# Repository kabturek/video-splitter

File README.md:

# Video Splitter

**This design is UNTESTED - the pcb was sent to the fab house 16.10.2016.**

This is a simple 2 channel video splitter for FPV use (but can be use with any analog signal).
It uses servo connectors for video in/out but you can solder wires directly to
the pads. Power pin is just a passthru between the 3 connectors (and it powers
the regulator). 

## Design

This is really a mashup of 2 reference designs - IA171 and LP2985 so no big
innovation here. According to the datasheet the IA171 can drive to 75ohm loads.

## Power supply

The splitter was designed to be powered by 5-16v if a 3.3v voltage regulator is used (LP2985 or mic5205). 
The IA171 can be powered by 2.8-5.5V so its possible to use it without any voltage regulator if you have a stable 
power supply in that range - bridge pins 1 and 5 (top pins) of the VREG and
applu 2.8-5.5v to any of the 3 pin connectors (middle pin).

## [BOM](BOM.csv)

| "Qty" | "Value"         | "Device"                        | "Package"   | "Parts"             | "Description"         | "Link" |
|-------|-----------------|---------------------------------|-------------|---------------------|-----------------------|----|
| "3"   | ""              | "M03LOCK"                       | "1X03_LOCK" | "VIN, VOUT1, VOUT2" | "Header 3"            | "" |
| "1"   | "0.1uF"         | "CAP0805"                       | "0805"      | "C1"                | "Capacitor"           | "" |
| "1"   | "100uF"         | "CAP_POL3528"                   | "EIA3528"   | "C3"                | "Capacitor Polarized" | "" |
| "1"   | "10nF"          | "CERAMIC-10NF-50V-5%-X7R(0805)" | "C0805"     | "C7"                | "302010175"           | "" |
| "3"   | "22uF"          | "CAP_POL1206"                   | "EIA3216"   | "C2, C4, C6"        | "Capacitor Polarized" | "" |
| "3"   | "75R"           | "RESISTOR0805-RES"              | "0805"      | "R1, R2, R3"        | "Resistor"            | "" |
| "1"   | "IA171"         | "IA171"                         | "SOT23-6"   | "U$1"               | ""                    | "" |
| "1"   | "LP2985-33DBVR" | "PMIC-LP2985-33DBVR(SOT23-5)"   | "SOT-23-5"  | "VREG"              | "310030033"           | "" |

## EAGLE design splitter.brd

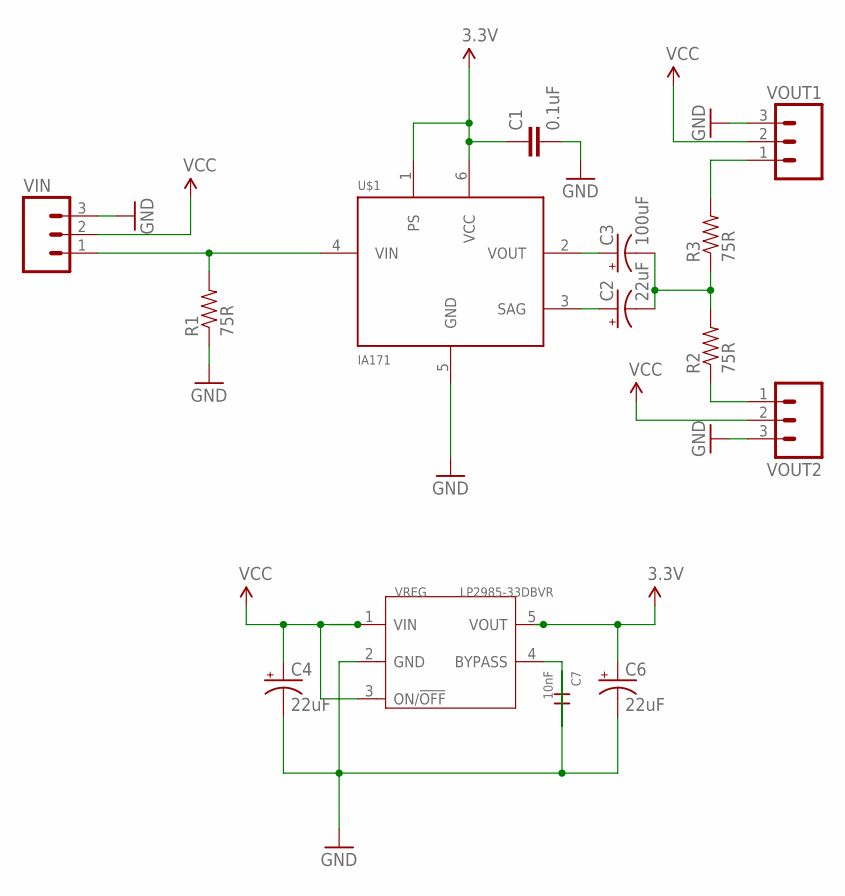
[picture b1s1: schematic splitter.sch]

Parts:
C1: 0.1uF; 0805
C2, C4, C6: 22uF; EIA3216
C3: 100uF; EIA3528
C7: 10nF; C0805
R1, R2, R3: 75R; 0805
U$1: IA171; SOT23-6
VIN: M03LOCK; 1X03_LOCK
VOUT1, VOUT2: M03LOCK; 1X03_LOCK
VREG: LP2985-33DBVR; SOT-23-5

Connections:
3.3V: C1.1, C6.A (+), U$1.1 (PS), U$1.6 (VCC), VREG.5 (VOUT)
GND: C1.2, C4.C (-), C6.C (-), C7.1, R1.1, U$1.5 (GND), VIN.3, VOUT1.3, VOUT2.3, VREG.2 (GND)
unnamed: C7.2, VREG.4 (BYPASS)
unnamed: R2.1, VOUT2.1
unnamed: R3.2, VOUT1.1
unnamed: C3.A (+), U$1.2 (VOUT)
unnamed: C2.A (+), U$1.3 (SAG)
unnamed: C2.C (-), C3.C (-), R2.2, R3.1
unnamed: R1.2, U$1.4 (VIN), VIN.1
VCC: C4.A (+), VIN.2, VOUT1.2, VOUT2.2, VREG.1 (VIN), VREG.3 (ON/!OFF)

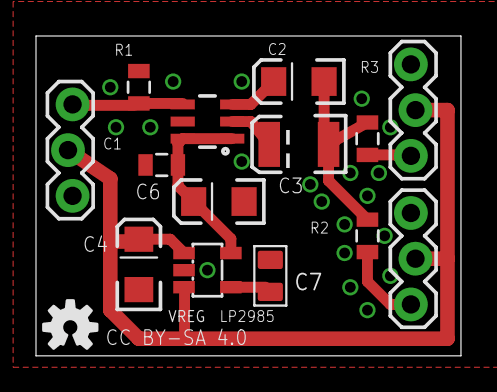
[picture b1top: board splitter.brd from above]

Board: 2 copper layers, 23.6 x 17.8 mm, 16 parts (1 on the bottom side), 10 nets.

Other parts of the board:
U$2, U$3: OSHW-LOGO-S

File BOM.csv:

"Qty";"Value";"Device";"Package";"Parts";"Description";"";
"3";"";"M03LOCK";"1X03_LOCK";"VIN, VOUT1, VOUT2";"Header 3";"";
"1";"0.1uF";"CAP0805";"0805";"C1";"Capacitor";"";
"1";"100uF";"CAP_POL3528";"EIA3528";"C3";"Capacitor Polarized";"";
"1";"10nF";"CERAMIC-10NF-50V-5%-X7R(0805)";"C0805";"C7";"302010175";"";
"3";"22uF";"CAP_POL1206";"EIA3216";"C2, C4, C6";"Capacitor Polarized";"";
"3";"75R";"RESISTOR0805-RES";"0805";"R1, R2, R3";"Resistor";"";
"1";"IA171";"IA171";"SOT23-6";"U$1";"";"";
"1";"LP2985-33DBVR";"PMIC-LP2985-33DBVR(SOT23-5)";"SOT-23-5";"VREG";"310030033";"";

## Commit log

2016-10-16 Add Video splitter schematic and board files
2016-10-16 Added docs and README/LICENSE
2016-10-16 README update
2016-10-16 Added gihub link to the board
2016-10-17 Standardized the capacitors and increased their values for VREG IN/OUT
2016-10-17 ERC changes
2016-10-17 fixed schematic layout
2016-10-17 cosmetic changes on the board layout
2016-10-17 last minute changes
2016-10-20 Added BOM
2016-10-20 update BOM after fixing component values
2016-10-20 fixed cap values
2016-10-20 added gerber files generated for Seeedstudio

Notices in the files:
splitter.brd:
CC BY-SA 4.0
parts and their libraries:
SparkFun-Passives: Licensing: Creative Commons ShareAlike 4.0 International - https://creativecommons.org/licenses/by-sa/4.0
